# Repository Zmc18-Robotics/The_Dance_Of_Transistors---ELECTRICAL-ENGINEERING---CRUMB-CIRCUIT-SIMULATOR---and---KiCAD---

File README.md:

# The Dance Of Transistors --- ELECTRICAL ENGINEERING --- CRUMB CIRCUIT SIMULATOR --- and --- KiCAD ---
✨one of my big electronic project that using so much transistors and electrical systems✨

---

# Here the pictures :

here I use 2 power supplies, one is "5.4v" and another one is "5.0v". but you actually can use 1 only, but yeah the game is kinda buggy so i use 2 for the different voltage

---

# Electrical Circuit :

---

# Description

some transistors used in this big project, some of them are for the fast blinker, and some of them are for the Arduino systems

used to be the knowledge of transistor systems, Seems complex but it's actually easy, just like switch but it's more electronic

Here the materials :
- Breadboard x4
- Arduino Nano x1
- LED pin x55
- Resistor 220Ω x13
- Resistor 1000Ω x1
- Resistor 1000000Ω x1
- Transistor NPN x6
- Transistor PNP x1
- Passive Buzzer x1
- Switch SPST x2
- Push Button x2
- Power Supply x ( 1 or 2 )
- Capacitor 3.3µF x1

---

ELECTRICITY!✨~ ☆*: .｡. o(≧▽≦)o .｡.:*☆

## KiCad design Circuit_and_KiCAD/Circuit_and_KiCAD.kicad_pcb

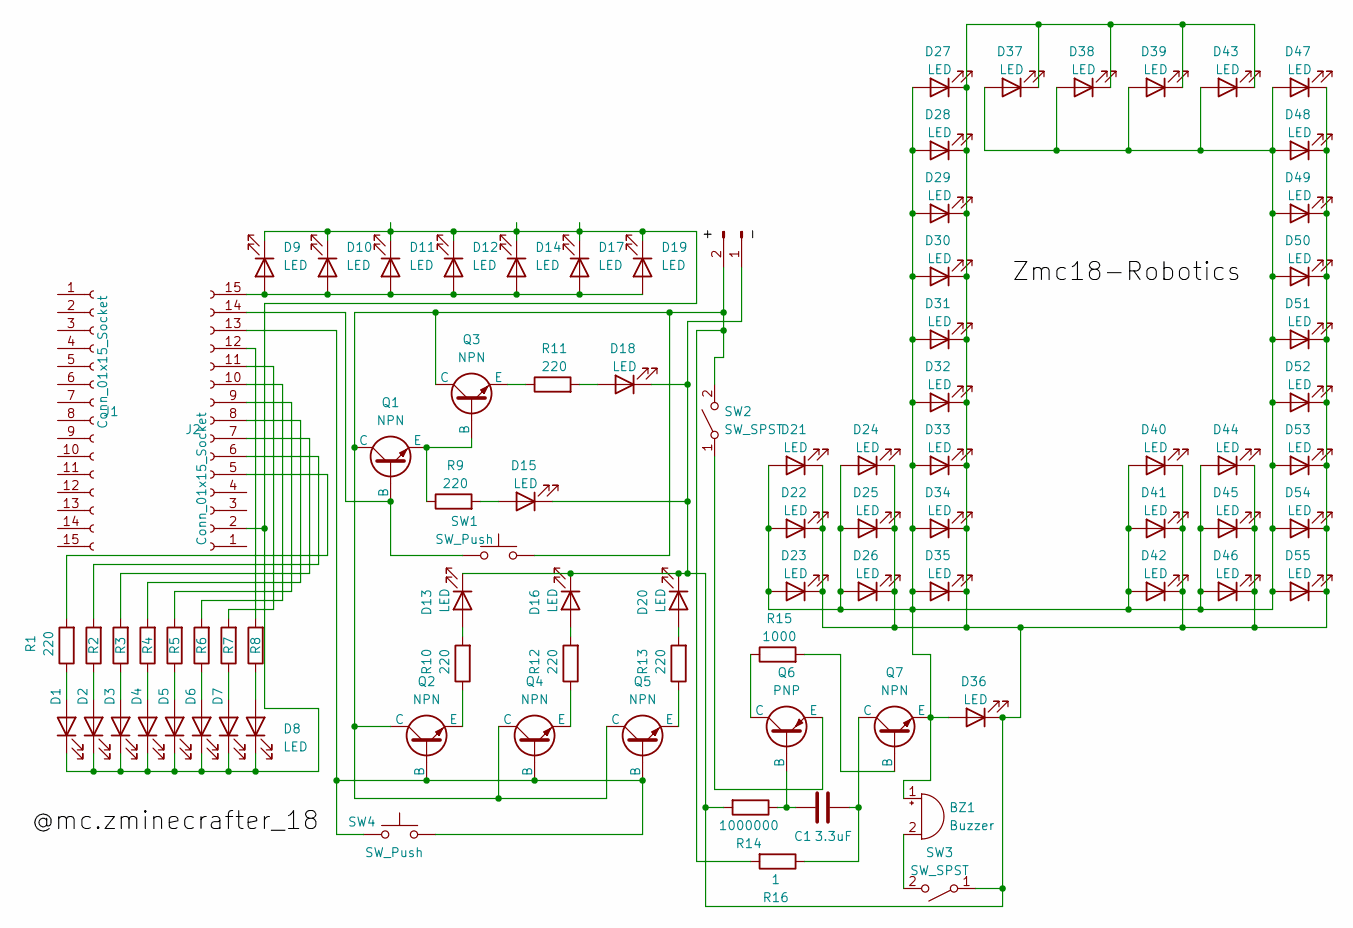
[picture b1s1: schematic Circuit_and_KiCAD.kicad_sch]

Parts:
+1: Conn_01x02_Pin; PinHeader_1x02_P2.54mm_Horizontal
BZ1: Buzzer; Buzzer_12x9.5RM7.6
C1: 3.3uF; CP_Elec_6.3x3
D1, D2, D3, D4, D5, D6, D7, D8, D9, D10, D11, D12, D13, D14, D15, D16, D17, D18, D19, D20, D36: LED; LED_0805_2012Metric
D21, D22, D23, D24, D25, D26, D27, D28, D29, D30, D31, D32, D33, D34, D35, D37, D38, D39, D40, D41, D42, D43, D44, D45, D46, D47, D48, D49, D50, D51, D52, D53, D54, D55: LED; LED_D5.0mm
J1, J2: Conn_01x15_Socket; PinSocket_1x15_P2.54mm_Vertical
Q1, Q2, Q3, Q4, Q5, Q7: NPN; SOT-23
Q6: PNP; SOT-23
R1, R2, R3, R4, R5, R6, R7, R8, R9, R10, R11, R12, R13: 220; R_0805_2012Metric
R14: 1000000; R_0805_2012Metric
R15: 1000; R_0805_2012Metric
R16: 1; R_0805_2012Metric
SW1, SW4: SW_Push; SW_PUSH_6mm
SW2, SW3: SW_SPST; SW_Slide-03_Wuerth-WS-SLTV_10x2.5x6.4_P2.54mm

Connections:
unnamed: +1.1, D13.1 (K), D15.1 (K), D16.1 (K), D18.1 (K), D20.1 (K), D21.1 (K), D22.1 (K), D23.1 (K), D24.1 (K), D25.1 (K), D26.1 (K), D27.1 (K), D28.1 (K), D29.1 (K), D30.1 (K), D31.1 (K), D32.1 (K), D33.1 (K), D34.1 (K), D35.1 (K), D36.1 (K), D37.1 (K), D38.1 (K), D39.1 (K), D40.1 (K), D41.1 (K), D42.1 (K), D43.1 (K), D44.1 (K), D45.1 (K), D46.1 (K), D47.1 (K), D48.1 (K), D49.1 (K), D50.1 (K), D51.1 (K), D52.1 (K), D53.1 (K), D54.1 (K), D55.1 (K), R14.2, SW3.1 (A)
unnamed: +1.2, Q1.1 (C), Q2.1 (C), Q3.1 (C), Q4.1 (C), Q5.1 (C), R16.2, SW1.2, SW2.2 (B)
unnamed: BZ1.1 (+), D21.2 (A), D22.2 (A), D23.2 (A), D24.2 (A), D25.2 (A), D26.2 (A), D27.2 (A), D28.2 (A), D29.2 (A), D30.2 (A), D31.2 (A), D32.2 (A), D33.2 (A), D34.2 (A), D35.2 (A), D36.2 (A), D37.2 (A), D38.2 (A), D39.2 (A), D40.2 (A), D41.2 (A), D42.2 (A), D43.2 (A), D44.2 (A), D45.2 (A), D46.2 (A), D47.2 (A), D48.2 (A), D49.2 (A), D50.2 (A), D51.2 (A), D52.2 (A), D53.2 (A), D54.2 (A), D55.2 (A), Q7.3 (E)
unnamed: BZ1.2 (-), SW3.2 (B)
unnamed: D1.2 (A), R1.1
unnamed: D1.1 (K), D2.1 (K), D3.1 (K), D4.1 (K), D5.1 (K), D6.1 (K), D7.1 (K), D8.1 (K), D9.1 (K), D10.1 (K), D11.1 (K), D12.1 (K), D14.1 (K), D17.1 (K), D19.1 (K), J2.2
unnamed: D2.2 (A), R2.1
unnamed: D3.2 (A), R3.1
unnamed: D4.2 (A), R4.1
unnamed: D5.2 (A), R5.1
unnamed: D6.2 (A), R6.1
unnamed: D7.2 (A), R7.1
unnamed: D8.2 (A), R8.1
unnamed: D9.2 (A), D10.2 (A), D11.2 (A), D12.2 (A), D14.2 (A), D17.2 (A), D19.2 (A), J2.15
unnamed: D13.2 (A), R10.2
unnamed: D15.2 (A), R9.2
unnamed: D16.2 (A), R12.2
unnamed: D18.2 (A), R11.2
unnamed: D20.2 (A), R13.2
unnamed: J2.5, R1.2
unnamed: J2.6, R2.2
unnamed: J2.7, R3.2
unnamed: J2.8, R4.2
unnamed: J2.9, R5.2
unnamed: J2.10, R6.2
unnamed: J2.11, R7.2
unnamed: J2.12, R8.2
unnamed: J2.13, Q2.2 (B), Q4.2 (B), Q5.2 (B), SW4.1, SW4.2
unnamed: J2.14, Q1.2 (B), SW1.1
unnamed: Q1.3 (E), Q3.2 (B), R9.1
unnamed: Q2.3 (E), R10.1
unnamed: Q3.3 (E), R11.1
unnamed: Q4.3 (E), R12.1
unnamed: Q5.3 (E), R13.1
unnamed: C1.2, Q6.2 (B), R14.1
unnamed: Q6.1 (C), R15.1
unnamed: Q6.3 (E), SW2.1 (A)
unnamed: Q7.2 (B), R15.2
unnamed: C1.1, Q7.1 (C), R16.1

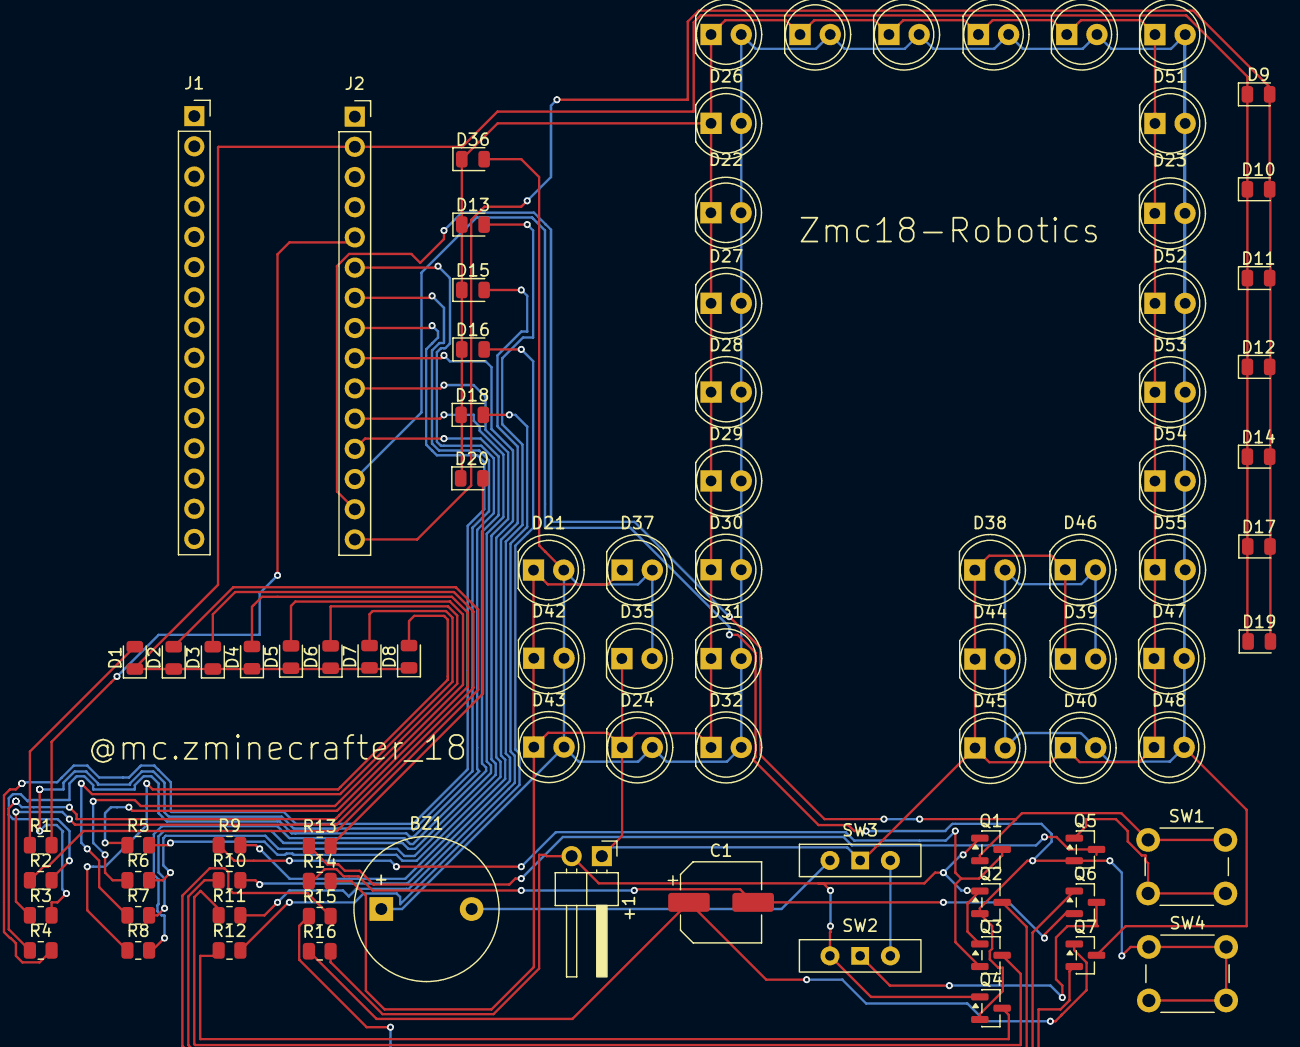
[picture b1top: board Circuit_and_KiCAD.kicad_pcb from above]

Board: 2 copper layers, 87 parts (0 on the bottom side), 39 nets.

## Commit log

2026-02-12 Add capacitor to components list
    Add capacitor to the list of components.
2026-02-12 Fix grammar in README description
    Corrected grammatical errors in the description section.
2026-05-10 Circuit and descriptions
    Replaced old image links with new image tags in README.
2026-05-10 Circuit and description
